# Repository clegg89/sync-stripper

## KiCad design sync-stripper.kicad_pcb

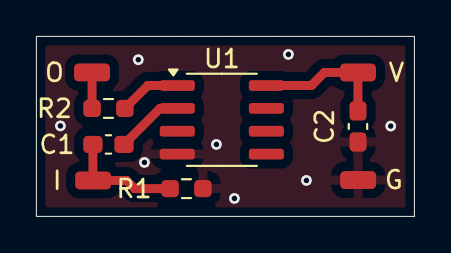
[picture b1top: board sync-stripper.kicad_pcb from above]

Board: 2 copper layers, 21.0 x 10.0 mm, 9 parts (0 on the bottom side), 6 nets.

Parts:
C1, C2: 100n; C_0603_1608Metric_Pad1.08x0.95mm_HandSolder
G: GND; SolderWirePad_1x01_SMD_1x2mm
I: VIDEO; SolderWirePad_1x01_SMD_1x2mm
O: SYNC; SolderWirePad_1x01_SMD_1x2mm
R1: 75; R_0603_1608Metric_Pad0.98x0.95mm_HandSolder
R2: 470; R_0603_1608Metric_Pad0.98x0.95mm_HandSolder
U1: LM1881; SOIC-8_3.9x4.9mm_P1.27mm
V: 5V; SolderWirePad_1x01_SMD_1x2mm

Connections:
+5V: C2.1, U1.8 (VCC), V.1
GND: C2.2, G.1, R1.2, U1.4 (GND)
unnamed: O.1, R2.2
unnamed: C1.2, I.1, R1.1
unnamed: R2.1, U1.1 (CSOUT)
unnamed: C1.1, U1.2 (CVIN)

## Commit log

2025-03-27 Initial version, basic stripper board
2025-03-28 Use ground/vcc symbols rather than labels
2025-03-29 More compact design
2025-03-29 As compact as I can get it
2025-03-29 No but really, super tiny
2025-03-29 More sensible layout
2025-07-11 Add BOM
2025-07-12 Remove KiCad BOM, remove Rset usage, add second ground plane and ground vias
